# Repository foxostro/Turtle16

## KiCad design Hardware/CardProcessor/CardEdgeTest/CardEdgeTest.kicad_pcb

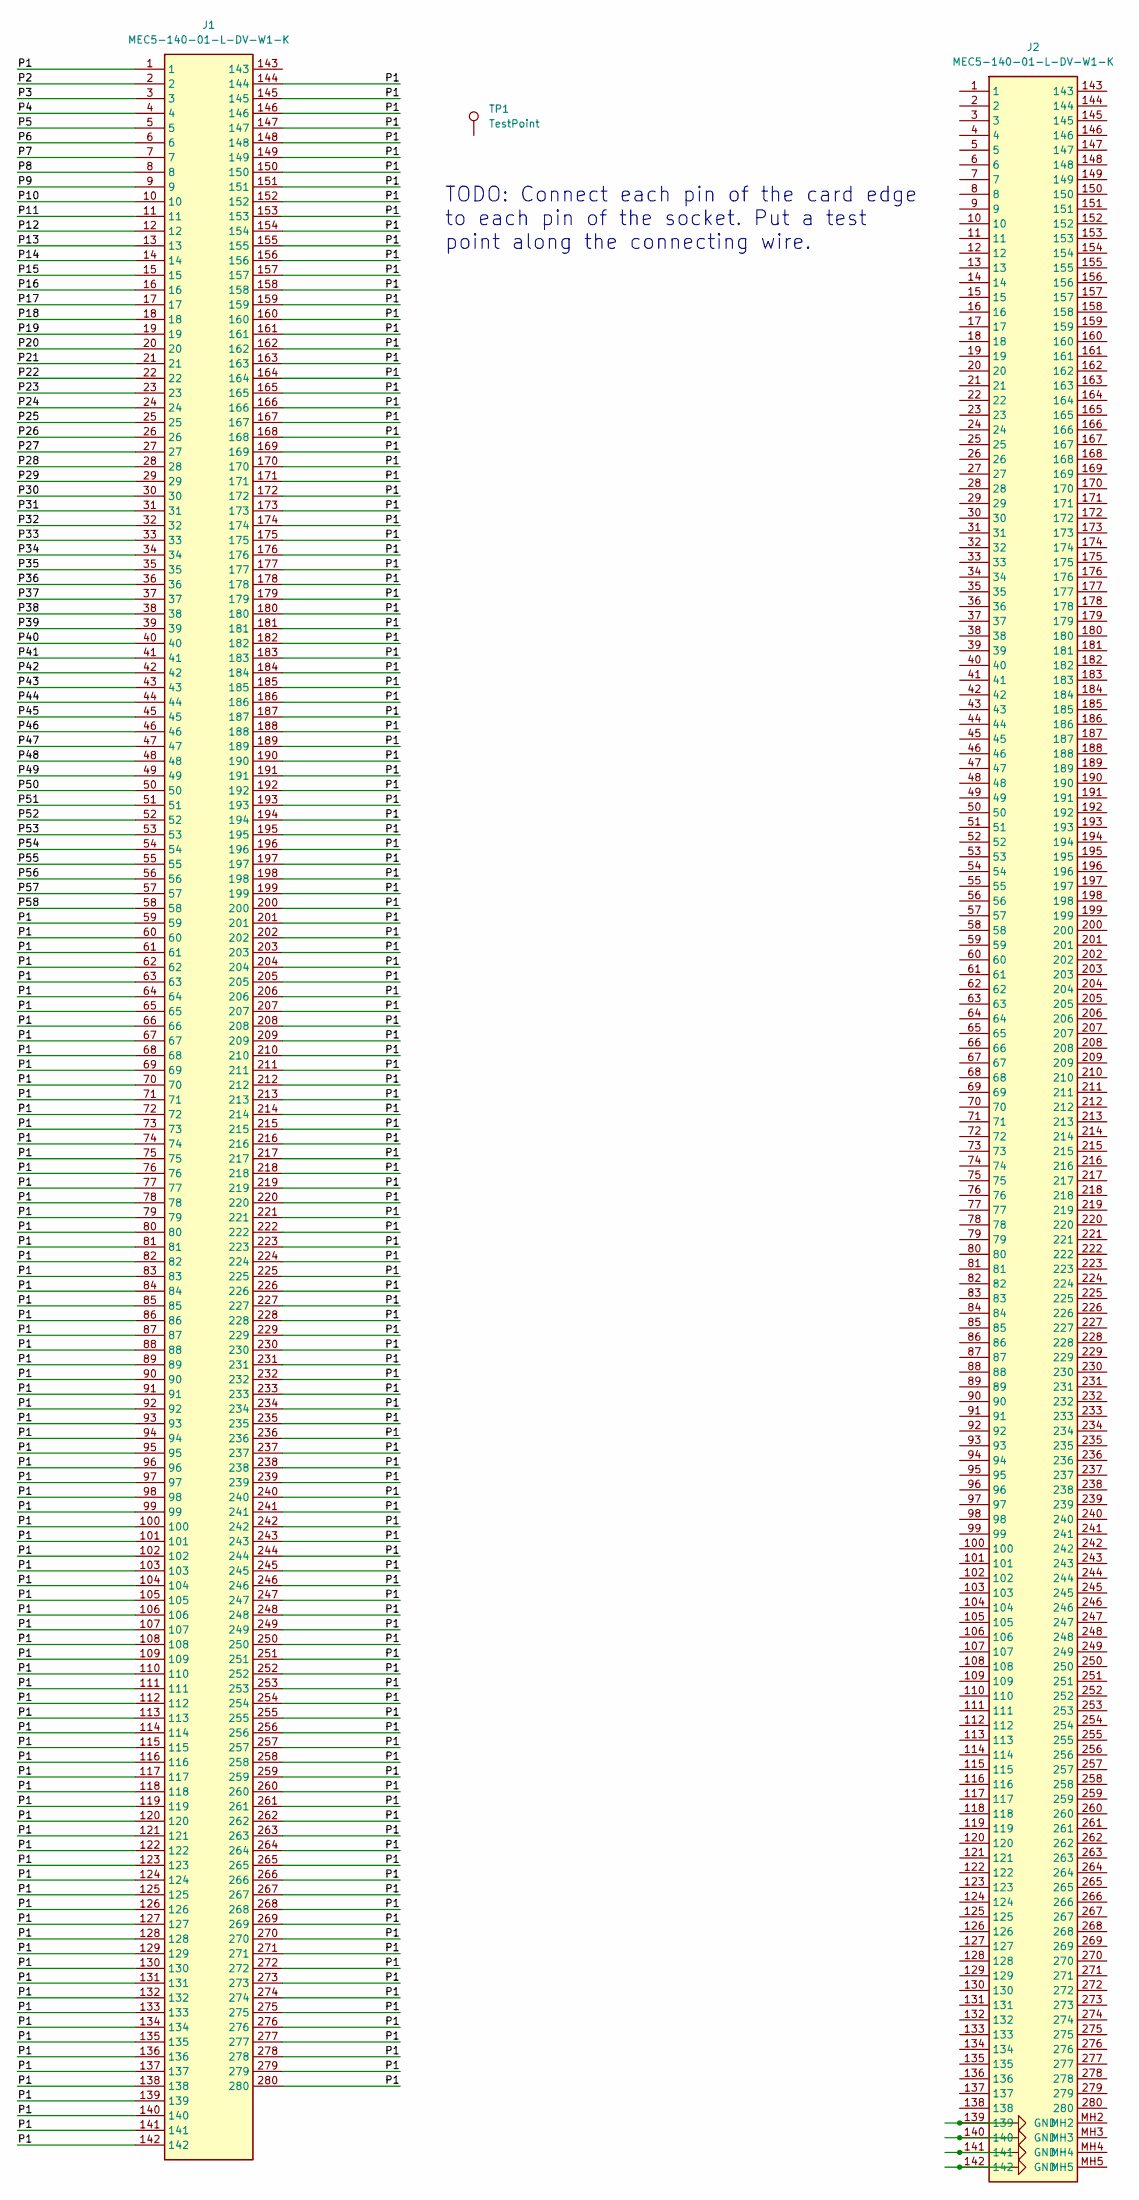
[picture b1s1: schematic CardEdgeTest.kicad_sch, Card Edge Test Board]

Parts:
J1: MEC5-140-01-L-DV-W1-K; MEC5-140-01-L-DV-W1-K_Edge; Mouser Part Number 200-MEC514001LDVW1K
J2: MEC5-140-01-L-DV-W1-K; MEC514001LDVW1K; Mouser Part Number 200-MEC514001LDVW1K
TP1: TestPoint; TestPoint_Pad_D1.0mm

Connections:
/P1: J1.1, J1.59, J1.60, J1.61, J1.62, J1.63, J1.64, J1.65, J1.66, J1.67, J1.68, J1.69, J1.70, J1.71, J1.72, J1.73, J1.74, J1.75, J1.76, J1.77, J1.78, J1.79, J1.80, J1.81, J1.82, J1.83, J1.84, J1.85, J1.86, J1.87, J1.88, J1.89, J1.90, J1.91, J1.92, J1.93, J1.94, J1.95, J1.96, J1.97, J1.98, J1.99, J1.100, J1.101, J1.102, J1.103, J1.104, J1.105, J1.106, J1.107, J1.108, J1.109, J1.110, J1.111, J1.112, J1.113, J1.114, J1.115, J1.116, J1.117, J1.118, J1.119, J1.120, J1.121, J1.122, J1.123, J1.124, J1.125, J1.126, J1.127, J1.128, J1.129, J1.130, J1.131, J1.132, J1.133, J1.134, J1.135, J1.136, J1.137, J1.138, J1.139, J1.140, J1.141, J1.142, J1.144, J1.145, J1.146, J1.147, J1.148, J1.149, J1.150, J1.151, J1.152, J1.153, J1.154, J1.155, J1.156, J1.157, J1.158, J1.159, J1.160, J1.161, J1.162, J1.163, J1.164, J1.165, J1.166, J1.167, J1.168, J1.169, J1.170, J1.171, J1.172, J1.173, J1.174, J1.175, J1.176, J1.177, J1.178, J1.179, J1.180, J1.181, J1.182, J1.183, J1.184, J1.185, J1.186, J1.187, J1.188, J1.189, J1.190, J1.191, J1.192, J1.193, J1.194, J1.195, J1.196, J1.197, J1.198, J1.199, J1.200, J1.201, J1.202, J1.203, J1.204, J1.205, J1.206, J1.207, J1.208, J1.209, J1.210, J1.211, J1.212, J1.213, J1.214, J1.215, J1.216, J1.217, J1.218, J1.219, J1.220, J1.221, J1.222, J1.223, J1.224, J1.225, J1.226, J1.227, J1.228, J1.229, J1.230, J1.231, J1.232, J1.233, J1.234, J1.235, J1.236, J1.237, J1.238, J1.239, J1.240, J1.241, J1.242, J1.243, J1.244, J1.245, J1.246, J1.247, J1.248, J1.249, J1.250, J1.251, J1.252, J1.253, J1.254, J1.255, J1.256, J1.257, J1.258, J1.259, J1.260, J1.261, J1.262, J1.263, J1.264, J1.265, J1.266, J1.267, J1.268, J1.269, J1.270, J1.271, J1.272, J1.273, J1.274, J1.275, J1.276, J1.277, J1.278, J1.279, J1.280
/P2: J1.2
/P3: J1.3
/P4: J1.4
/P5: J1.5
/P6: J1.6
/P7: J1.7
/P8: J1.8
/P9: J1.9
/P10: J1.10
/P11: J1.11
/P12: J1.12
/P13: J1.13
/P14: J1.14
/P15: J1.15
/P16: J1.16
/P17: J1.17
/P18: J1.18
/P19: J1.19
/P20: J1.20
/P21: J1.21
/P22: J1.22
/P23: J1.23
/P24: J1.24
/P25: J1.25
/P26: J1.26
/P27: J1.27
/P28: J1.28
/P29: J1.29
/P30: J1.30
/P31: J1.31
/P32: J1.32
/P33: J1.33
/P34: J1.34
/P35: J1.35
/P36: J1.36
/P37: J1.37
/P38: J1.38
/P39: J1.39
/P40: J1.40
/P41: J1.41
/P42: J1.42
/P43: J1.43
/P44: J1.44
/P45: J1.45
/P46: J1.46
/P47: J1.47
/P48: J1.48
/P49: J1.49
/P50: J1.50
/P51: J1.51
/P52: J1.52
/P53: J1.53
/P54: J1.54
/P55: J1.55
/P56: J1.56
/P57: J1.57
/P58: J1.58
GND: J2.139, J2.140, J2.141, J2.142

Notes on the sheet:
TODO: Connect each pin of the card edge to each pin of the socket. Put a test point along the connecting wire.

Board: 2 copper layers, 3 parts (0 on the bottom side), 2 nets, no tracks yet.

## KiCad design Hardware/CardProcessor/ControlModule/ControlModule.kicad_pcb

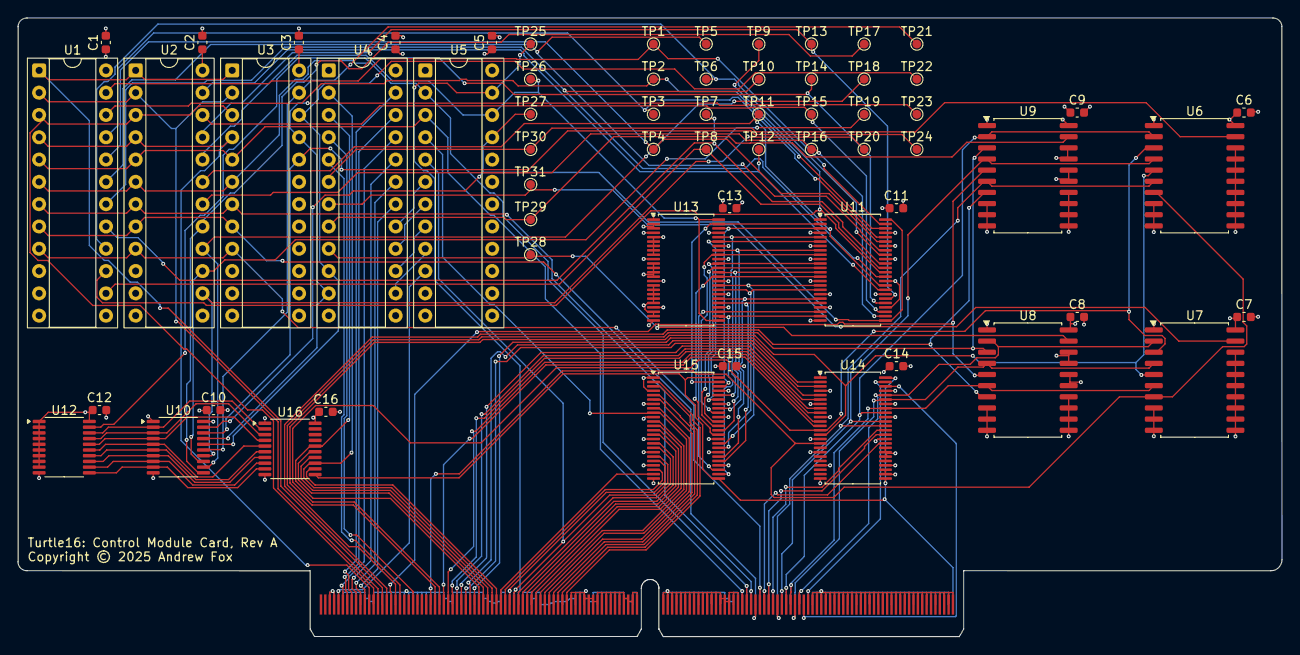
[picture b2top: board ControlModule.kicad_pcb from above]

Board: 4 copper layers, 144.0 x 70.5 mm, 64 parts (0 on the bottom side), 126 nets.

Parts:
C1, C2, C3, C4, C5, C6, C7, C8, C9, C10, C11, C12, C13, C14, C15, C16: 0.1uF; C_0603_1608Metric
J1: MEC5-140-01-L-DV-W1-K; MEC5-140-01-L-DV-W1-K_Edge
TP1: Ctl_Mid0; TestPoint_Pad_D1.0mm
TP2: Ctl_Mid1; TestPoint_Pad_D1.0mm
TP3: Ctl_Mid2; TestPoint_Pad_D1.0mm
TP4: Ctl_Mid3; TestPoint_Pad_D1.0mm
TP5: Ctl_Mid4; TestPoint_Pad_D1.0mm
TP6: Ctl_Mid5; TestPoint_Pad_D1.0mm
TP7: Ctl_Mid6; TestPoint_Pad_D1.0mm
TP8: Ctl_Mid7; TestPoint_Pad_D1.0mm
TP9: Ctl_Mid8; TestPoint_Pad_D1.0mm
TP10: Ctl_Mid9; TestPoint_Pad_D1.0mm
TP11: Ctl_Mid10; TestPoint_Pad_D1.0mm
TP12: Ctl_Mid11; TestPoint_Pad_D1.0mm
TP13: Ctl_Mid12; TestPoint_Pad_D1.0mm
TP14: Ctl_Mid13; TestPoint_Pad_D1.0mm
TP15: Ctl_Mid14; TestPoint_Pad_D1.0mm
TP16: Ctl_Mid15; TestPoint_Pad_D1.0mm
TP17: Ctl_Mid16; TestPoint_Pad_D1.0mm
TP18: Ctl_Mid17; TestPoint_Pad_D1.0mm
TP19: Ctl_Mid18; TestPoint_Pad_D1.0mm
TP20: Ctl_Mid19; TestPoint_Pad_D1.0mm
TP21: Ctl_Mid20; TestPoint_Pad_D1.0mm
TP22: Ctl_Mid21; TestPoint_Pad_D1.0mm
TP23: Ctl_Mid22; TestPoint_Pad_D1.0mm
TP24: Ctl_Mid23; TestPoint_Pad_D1.0mm
TP25: STALL; TestPoint_Pad_D1.0mm
TP26: ~{FLUSH}; TestPoint_Pad_D1.0mm
TP27: FLUSH; TestPoint_Pad_D1.0mm
TP28: SEL_B_MATCHES_SEL_C_MEM; TestPoint_Pad_D1.0mm
TP29: SEL_A_MATCHES_SEL_C_MEM; TestPoint_Pad_D1.0mm
TP30: SEL_A_MATCHES_SEL_C_EX; TestPoint_Pad_D1.0mm
TP31: SEL_B_MATCHES_SEL_C_EX; TestPoint_Pad_D1.0mm
U1, U2, U3, U4, U5: ATF22V10C-7PX; DIP-24_W7.62mm_Socket
U6, U7, U8, U9: 74F521; SOIC-20W_7.5x12.8mm_P1.27mm
U10, U12: 74ABT245; TSSOP-20_4.4x6.5mm_P0.65mm
U11, U13: 74ABT16245; TSSOP-48_6.1x12.5mm_P0.5mm
U14, U15: 74ABT16374; TSSOP-48_6.1x12.5mm_P0.5mm
U16: 74ABT574; TSSOP-20_4.4x6.5mm_P0.65mm

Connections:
/CardEdgeControl/Carry: J1.23, U1.4 (IN), U2.4 (IN), U3.4 (IN)
/CardEdgeControl/Ctl_MEM17: J1.43, U4.4 (IN)
/CardEdgeControl/Ctl_MEM20: J1.37, U4.5 (IN)
/CardEdgeControl/FWD_A: J1.11, U4.21 (I/O)
/CardEdgeControl/FWD_B: J1.17, U4.20 (I/O)
/CardEdgeControl/FWD_EX_TO_A: J1.13, U4.22 (I/O)
/CardEdgeControl/FWD_EX_TO_B: J1.19, U4.19 (I/O)
/CardEdgeControl/FWD_MEM_TO_A: J1.15, U4.23 (I/O)
/CardEdgeControl/FWD_MEM_TO_B: J1.21, U4.18 (I/O)
/CardEdgeControl/Ins_ID0: J1.213, J1.214, U14.47 (1D1)
/CardEdgeControl/Ins_ID1: J1.211, J1.212, U14.46 (1D2)
/CardEdgeControl/Ins_ID2: J1.209, J1.210, U7.2 (P0), U8.2 (P0), U14.44 (1D3)
/CardEdgeControl/Ins_ID3: J1.207, J1.208, U7.4 (P1), U8.4 (P1), U14.43 (1D4)
/CardEdgeControl/Ins_ID4: J1.205, J1.206, U7.6 (P2), U8.6 (P2), U14.41 (1D5)
/CardEdgeControl/Ins_ID5: J1.203, J1.204, U6.2 (P0), U9.2 (P0), U14.40 (1D6)
/CardEdgeControl/Ins_ID6: J1.201, J1.202, U6.4 (P1), U9.4 (P1), U14.38 (1D7)
/CardEdgeControl/Ins_ID7: J1.199, J1.200, U6.6 (P2), U9.6 (P2), U14.37 (1D8)
/CardEdgeControl/Ins_ID8: J1.197, J1.198, U14.36 (2D1)
/CardEdgeControl/Ins_ID9: J1.195, J1.196, U14.35 (2D2)
/CardEdgeControl/Ins_ID10: J1.193, J1.194, U14.33 (2D3)
/CardEdgeControl/Ins_ID11: J1.191, J1.192, U1.9 (IN), U2.9 (IN), U3.9 (IN)
/CardEdgeControl/Ins_ID12: J1.189, J1.190, U1.8 (IN), U2.8 (IN), U3.8 (IN)
/CardEdgeControl/Ins_ID13: J1.187, J1.188, U1.7 (IN), U2.7 (IN), U3.7 (IN)
/CardEdgeControl/Ins_ID14: J1.185, J1.186, U1.6 (IN), U2.6 (IN), U3.6 (IN), U5.2 (IN)
/CardEdgeControl/Ins_ID15: J1.183, J1.184, U1.5 (IN), U2.5 (IN), U3.5 (IN), U5.3 (IN)
/CardEdgeControl/N: J1.29, U1.1 (IN/CLK), U2.1 (IN/CLK), U3.1 (IN/CLK)
/CardEdgeControl/OVF: J1.27, U1.2 (IN), U2.2 (IN), U3.2 (IN)
/CardEdgeControl/Phi1c: J1.280, U14.25 (2CLK), U14.48 (1CLK), U15.25 (2CLK), U15.48 (1CLK), U16.11 (Cp)
/CardEdgeControl/SelC_MEM0: J1.35, U8.3 (Q0), U9.3 (Q0)
/CardEdgeControl/SelC_MEM1: J1.33, U8.5 (Q1), U9.5 (Q1)
/CardEdgeControl/SelC_MEM2: J1.31, U8.7 (Q2), U9.7 (Q2)
/CardEdgeControl/Z: J1.25, U1.3 (IN), U2.3 (IN), U3.3 (IN)
/CardEdgeControl/~RST_sync: J1.9, J1.10, U5.10 (IN)
/ID/Ctl_EX0: J1.113, U15.2 (1Q1)
/ID/Ctl_EX1: J1.111, U15.3 (1Q2)
/ID/Ctl_EX2: J1.109, U15.5 (1Q3)
/ID/Ctl_EX3: J1.107, U15.6 (1Q4)
/ID/Ctl_EX4: J1.105, U15.8 (1Q5)
/ID/Ctl_EX5: J1.103, U5.4 (IN), U15.9 (1Q6)
/ID/Ctl_EX6: J1.101, U15.11 (1Q7)
/ID/Ctl_EX7: J1.99, U15.12 (1Q8)
/ID/Ctl_EX8: J1.97, U15.13 (2Q1)
/ID/Ctl_EX9: J1.95, U15.14 (2Q2)
/ID/Ctl_EX10: J1.93, U15.16 (2Q3)
/ID/Ctl_EX11: J1.91, U15.17 (2Q4)
/ID/Ctl_EX12: J1.89, J1.90, U5.5 (IN), U15.19 (2Q5)
/ID/Ctl_EX13: J1.87, J1.88, U15.20 (2Q6)
/ID/Ctl_EX14: J1.85, U15.22 (2Q7)
/ID/Ctl_EX15: J1.83, U15.23 (2Q8)
/ID/Ctl_EX16: J1.81, U16.12 (Q7)
/ID/Ctl_EX17: J1.79, U4.2 (IN), U16.13 (Q6)
/ID/Ctl_EX18: J1.77, U16.14 (Q5)
/ID/Ctl_EX19: J1.75, U16.15 (Q4)
/ID/Ctl_EX20: J1.73, U4.3 (IN), U16.16 (Q3)
/ID/Ctl_Mid0: TP1.1, U1.23 (I/O), U11.47 (1A1)
/ID/Ctl_Mid1: TP2.1, U1.22 (I/O), U11.46 (1A2)
/ID/Ctl_Mid2: TP3.1, U1.21 (I/O), U11.44 (1A3)
/ID/Ctl_Mid3: TP4.1, U1.20 (I/O), U11.43 (1A4)
/ID/Ctl_Mid4: TP5.1, U1.19 (I/O), U11.41 (1A5)
/ID/Ctl_Mid5: TP6.1, U1.16 (I/O), U11.40 (1A6)
/ID/Ctl_Mid6: TP7.1, U1.17 (I/O), U11.38 (1A7)
/ID/Ctl_Mid7: TP8.1, U1.14 (I/O), U11.37 (1A8)
/ID/Ctl_Mid8: TP9.1, U1.15 (I/O), U11.36 (2A1)
/ID/Ctl_Mid9: TP10.1, U1.18 (I/O), U11.35 (2A2)
/ID/Ctl_Mid10: TP11.1, U2.19 (I/O), U11.33 (2A3)
/ID/Ctl_Mid11: TP12.1, U2.23 (I/O), U11.32 (2A4)
/ID/Ctl_Mid12: TP13.1, U2.21 (I/O), U11.30 (2A5)
/ID/Ctl_Mid13: TP14.1, U2.20 (I/O), U11.29 (2A6)
/ID/Ctl_Mid14: TP15.1, U2.22 (I/O), U11.27 (2A7)
/ID/Ctl_Mid15: TP16.1, U2.18 (I/O), U11.26 (2A8)
/ID/Ctl_Mid16: TP17.1, U2.17 (I/O), U10.11 (B7)
/ID/Ctl_Mid17: TP18.1, U2.16 (I/O), U10.12 (B6)
/ID/Ctl_Mid18: TP19.1, U2.15 (I/O), U10.13 (B5)
/ID/Ctl_Mid19: TP20.1, U2.14 (I/O), U10.14 (B4)
/ID/Ctl_Mid20: TP21.1, U3.23 (I/O), U10.15 (B3)
/ID/Ctl_Mid21: TP22.1, U3.22 (I/O), U4.10 (IN), U10.16 (B2)
/ID/Ctl_Mid22: TP23.1, U3.21 (I/O), U4.11 (IN), U10.17 (B1)
/ID/Ctl_Mid23: TP24.1, U3.20 (I/O), U10.18 (B0)
/ID/Hazard Control/FLUSH: TP27.1, U5.21 (I/O), U10.19 (CE), U11.25 (2~OE), U11.48 (1~OE)
/ID/Hazard Control/Hazard Control Comparators/SEL_A_MATCHES_SEL_C_EX: TP30.1, U4.6 (IN), U6.19 (~P=Q)
/ID/Hazard Control/Hazard Control Comparators/SEL_A_MATCHES_SEL_C_MEM: TP29.1, U4.8 (IN), U9.19 (~P=Q)
/ID/Hazard Control/Hazard Control Comparators/SEL_B_MATCHES_SEL_C_EX: TP31.1, U4.7 (IN), U7.19 (~P=Q)
/ID/Hazard Control/Hazard Control Comparators/SEL_B_MATCHES_SEL_C_MEM: TP28.1, U4.9 (IN), U8.19 (~P=Q)
/ID/Hazard Control/STALL: J1.92, TP25.1, U5.23 (I/O)
/ID/Hazard Control/~FLUSH: TP26.1, U5.22 (I/O), U12.19 (CE), U13.25 (2~OE), U13.48 (1~OE)
/ID/ID Flush/Ctl_ID0: U11.2 (1B1), U13.47 (1A1), U15.47 (1D1)
/ID/ID Flush/Ctl_ID1: U11.3 (1B2), U13.46 (1A2), U15.46 (1D2)
/ID/ID Flush/Ctl_ID2: U11.5 (1B3), U13.44 (1A3), U15.44 (1D3)
/ID/ID Flush/Ctl_ID3: U11.6 (1B4), U13.43 (1A4), U15.43 (1D4)
/ID/ID Flush/Ctl_ID4: U11.8 (1B5), U13.41 (1A5), U15.41 (1D5)
/ID/ID Flush/Ctl_ID5: U11.9 (1B6), U13.40 (1A6), U15.40 (1D6)
/ID/ID Flush/Ctl_ID6: U11.11 (1B7), U13.38 (1A7), U15.38 (1D7)
/ID/ID Flush/Ctl_ID7: U11.12 (1B8), U13.37 (1A8), U15.37 (1D8)
/ID/ID Flush/Ctl_ID8: U11.13 (2B1), U13.36 (2A1), U15.36 (2D1)
/ID/ID Flush/Ctl_ID9: U11.14 (2B2), U13.35 (2A2), U15.35 (2D2)
/ID/ID Flush/Ctl_ID10: U11.16 (2B3), U13.33 (2A3), U15.33 (2D3)
/ID/ID Flush/Ctl_ID11: U11.17 (2B4), U13.32 (2A4), U15.32 (2D4)
/ID/ID Flush/Ctl_ID12: U11.19 (2B5), U13.30 (2A5), U15.30 (2D5)
/ID/ID Flush/Ctl_ID13: U11.20 (2B6), U13.29 (2A6), U15.29 (2D6)
/ID/ID Flush/Ctl_ID14: U11.22 (2B7), U13.27 (2A7), U15.27 (2D7)
/ID/ID Flush/Ctl_ID15: U11.23 (2B8), U13.26 (2A8), U15.26 (2D8)
/ID/ID Flush/Ctl_ID16: U10.9 (A7), U12.11 (B7), U16.9 (D7)
/ID/ID Flush/Ctl_ID17: U10.8 (A6), U12.12 (B6), U16.8 (D6)
/ID/ID Flush/Ctl_ID18: U10.7 (A5), U12.13 (B5), U16.7 (D5)
/ID/ID Flush/Ctl_ID19: U10.6 (A4), U12.14 (B4), U16.6 (D4)
/ID/ID Flush/Ctl_ID20: U10.5 (A3), U12.15 (B3), U16.5 (D3)
/ID/ID Flush/Ctl_ID21: U10.4 (A2), U12.16 (B2), U16.4 (D2)
/ID/ID Flush/Ctl_ID22: U10.3 (A1), U12.17 (B1), U16.3 (D1)
/ID/ID Flush/Ctl_ID23: U10.2 (A0), U12.18 (B0), U16.2 (D0)
/ID/Ins_EX0: J1.71, U14.2 (1Q1)
/ID/Ins_EX1: J1.69, U14.3 (1Q2)
/ID/Ins_EX2: J1.67, U14.5 (1Q3)
/ID/Ins_EX3: J1.65, U14.6 (1Q4)
/ID/Ins_EX4: J1.63, U14.8 (1Q5)
/ID/Ins_EX5: J1.61, U14.9 (1Q6)
/ID/Ins_EX6: J1.59, U14.11 (1Q7)
/ID/Ins_EX7: J1.57, U14.12 (1Q8)
/ID/Ins_EX8: J1.55, U6.3 (Q0), U7.3 (Q0), U14.13 (2Q1)
/ID/Ins_EX9: J1.53, U6.5 (Q1), U7.5 (Q1), U14.14 (2Q2)
/ID/Ins_EX10: J1.51, U6.7 (Q2), U7.7 (Q2), U14.16 (2Q3)
GND: C1.2, C2.2, C3.2, C4.2, C5.2, C6.2, C7.2, C8.2, C9.2, C10.2, C11.2, C12.2, C13.2, C14.2, C15.2, C16.2, J1.12, J1.14, J1.16, J1.18, J1.20, J1.22, J1.24, J1.26, J1.28, J1.30, J1.32, J1.34, J1.36, J1.38, J1.40, J1.42, J1.44, J1.46, J1.48, J1.50, J1.52, J1.54, J1.56, J1.58, J1.60, J1.62, J1.64, J1.66, J1.68, J1.70, J1.72, J1.74, J1.76, J1.78, J1.80, J1.82, J1.84, J1.86, J1.94, J1.96, J1.98, J1.100, J1.102, J1.104, J1.106, J1.108, J1.110, J1.112, J1.114, J1.115, J1.116, J1.117, J1.118, J1.119, J1.120, J1.121, J1.122, J1.123, J1.124, J1.125, J1.126, J1.127, J1.128, J1.129, J1.130, J1.131, J1.132, J1.133, J1.134, J1.135, J1.136, J1.137, J1.138, J1.139, J1.140, J1.141, J1.142, J1.143, J1.144, J1.145, J1.146, J1.147, J1.148, J1.149, J1.150, J1.151, J1.152, J1.153, J1.154, J1.155, J1.156, J1.157, J1.158, J1.159, J1.160, J1.161, J1.162, J1.163, J1.164, J1.165, J1.166, J1.167, J1.168, J1.169, J1.170, J1.171, J1.172, J1.173, J1.174, J1.175, J1.176, J1.177, J1.178, J1.179, J1.180, J1.181, J1.182, J1.215, J1.216, J1.217, J1.218, J1.219, J1.220, J1.221, J1.222, J1.223, J1.224, J1.225, J1.226, J1.227, J1.228, J1.229, J1.230, J1.231, J1.232, J1.233, J1.234, J1.235, J1.236, J1.237, J1.238, J1.239, J1.240, J1.241, J1.242, J1.243, J1.244, J1.245, J1.246, J1.247, J1.248, J1.249, J1.250, J1.251, J1.252, J1.253, J1.254, J1.255, J1.256, J1.257, J1.258, J1.259, J1.260, J1.261, J1.262, J1.263, J1.264, J1.265, J1.266, J1.267, J1.268, J1.269, J1.270, J1.271, J1.272, J1.273, J1.274, J1.275, J1.276, J1.277, J1.278, J1.279, U1.10 (IN), U1.11 (IN), U1.12 (GND), U2.10 (IN), U2.11 (IN), U2.12 (GND), U3.10 (IN), U3.11 (IN), U3.12 (GND), U4.1 (IN/CLK), U4.12 (GND), U5.1 (IN/CLK), U5.12 (GND), U5.15 (I/O), U6.1 (~OE), U6.8 (P3), U6.9 (Q3), U6.10 (GND), U6.11 (P4), U6.12 (Q4), U6.13 (P5), U6.14 (Q5), U6.15 (P6), U6.16 (Q6), U6.17 (P7), U6.18 (Q7), U7.1 (~OE), U7.8 (P3), U7.9 (Q3), U7.10 (GND), U7.11 (P4), U7.12 (Q4), U7.13 (P5), U7.14 (Q5), U7.15 (P6), U7.16 (Q6), U7.17 (P7), U7.18 (Q7), U8.1 (~OE), U8.8 (P3), U8.9 (Q3), U8.10 (GND), U8.11 (P4), U8.12 (Q4), U8.13 (P5), U8.14 (Q5), U8.15 (P6), U8.16 (Q6), U8.17 (P7), U8.18 (Q7), U9.1 (~OE), U9.8 (P3), U9.9 (Q3), U9.10 (GND), U9.11 (P4), U9.12 (Q4), U9.13 (P5), U9.14 (Q5), U9.15 (P6), U9.16 (Q6), U9.17 (P7), U9.18 (Q7), U10.1 (A->B), U10.10 (GND), U11.4 (GND), U11.10 (GND), U11.15 (GND), U11.21 (GND), U11.28 (GND), U11.34 (GND), U11.39 (GND), U11.45 (GND), U12.10 (GND), U13.1 (1DIR), U13.4 (GND), U13.10 (GND), U13.15 (GND), U13.21 (GND), U13.24 (2DIR), U13.28 (GND), U13.34 (GND), U13.39 (GND), U13.45 (GND), U14.1 (1~OE), U14.4 (GND), U14.10 (GND), U14.15 (GND), U14.21 (GND), U14.24 (2~OE), U14.28 (GND), U14.34 (GND), U14.39 (GND), U14.45 (GND), U15.1 (1~OE), U15.4 (GND), U15.10 (GND), U15.15 (GND), U15.21 (GND), U15.24 (2~OE), U15.28 (GND), U15.34 (GND), U15.39 (GND), U15.45 (GND), U16.1 (OE), U16.10 (GND)
unnamed: U4.14 (I/O), U5.9 (IN)
unnamed: U4.15 (I/O), U5.8 (IN)
unnamed: U4.16 (I/O), U5.7 (IN)
unnamed: U4.17 (I/O), U5.6 (IN)
VCC: C1.1, C2.1, C3.1, C4.1, C5.1, C6.1, C7.1, C8.1, C9.1, C10.1, C11.1, C12.1, C13.1, C14.1, C15.1, C16.1, J1.5, J1.6, J1.7, J1.8, U1.24 (VCC), U2.24 (VCC), U3.24 (VCC), U4.24 (VCC), U5.24 (VCC), U6.20 (VCC), U7.20 (VCC), U8.20 (VCC), U9.20 (VCC), U10.20 (VCC), U11.1 (1DIR), U11.7 (VCC), U11.18 (VCC), U11.24 (2DIR), U11.31 (VCC), U11.42 (VCC), U12.1 (A->B), U12.2 (A0), U12.3 (A1), U12.4 (A2), U12.5 (A3), U12.6 (A4), U12.7 (A5), U12.8 (A6), U12.9 (A7), U12.20 (VCC), U13.2 (1B1), U13.3 (1B2), U13.5 (1B3), U13.6 (1B4), U13.7 (VCC), U13.8 (1B5), U13.9 (1B6), U13.11 (1B7), U13.12 (1B8), U13.13 (2B1), U13.14 (2B2), U13.16 (2B3), U13.17 (2B4), U13.18 (VCC), U13.19 (2B5), U13.20 (2B6), U13.22 (2B7), U13.23 (2B8), U13.31 (VCC), U13.42 (VCC), U14.7 (VCC), U14.18 (VCC), U14.26 (2D8), U14.27 (2D7), U14.29 (2D6), U14.30 (2D5), U14.31 (VCC), U14.32 (2D4), U14.42 (VCC), U15.7 (VCC), U15.18 (VCC), U15.31 (VCC), U15.42 (VCC), U16.20 (VCC)

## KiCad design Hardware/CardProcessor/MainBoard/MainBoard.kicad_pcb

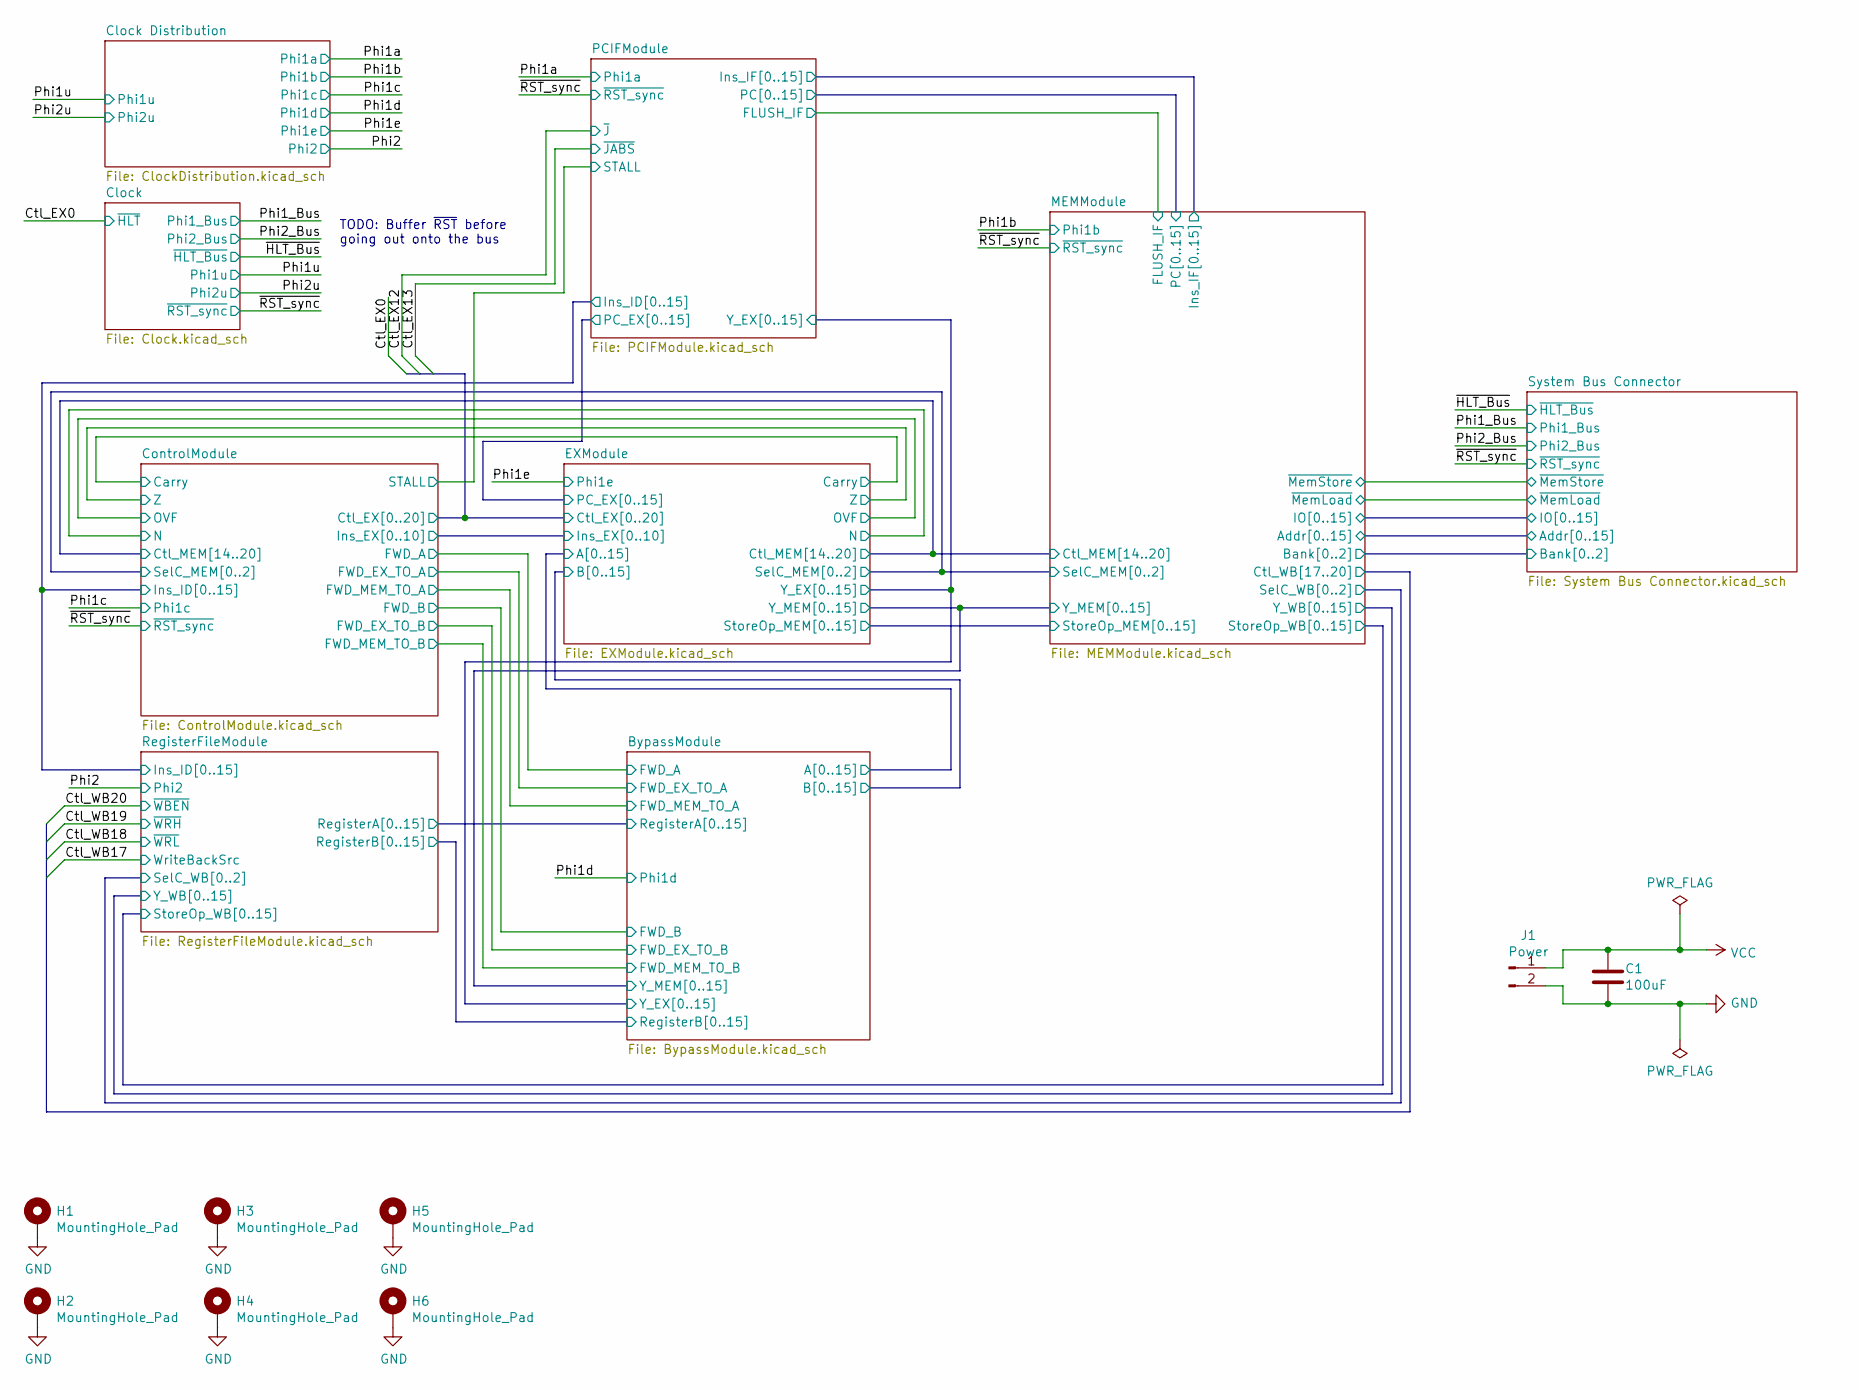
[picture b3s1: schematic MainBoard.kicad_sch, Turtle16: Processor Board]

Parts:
C1: 100uF; C_1206_3216Metric; Manufacturer# AMK316ABJ107ML-T; Mouser# 963-AMK316ABJ107ML-T
H1, H2, H3, H4, H5, H6: MountingHole_Pad; MountingHole_3.2mm_M3_Pad
J1: Power; 172448-0002; Manufacturer# 172448-0002; Mouser# 538-172448-0002

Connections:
GND: C1.2, H1.1, H2.1, H3.1, H4.1, H5.1, H6.1, J1.2; also elsewhere on the board
VCC: C1.1, J1.1; also elsewhere on the board

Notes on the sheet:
TODO: Buffer ~{RST} before going out onto the bus

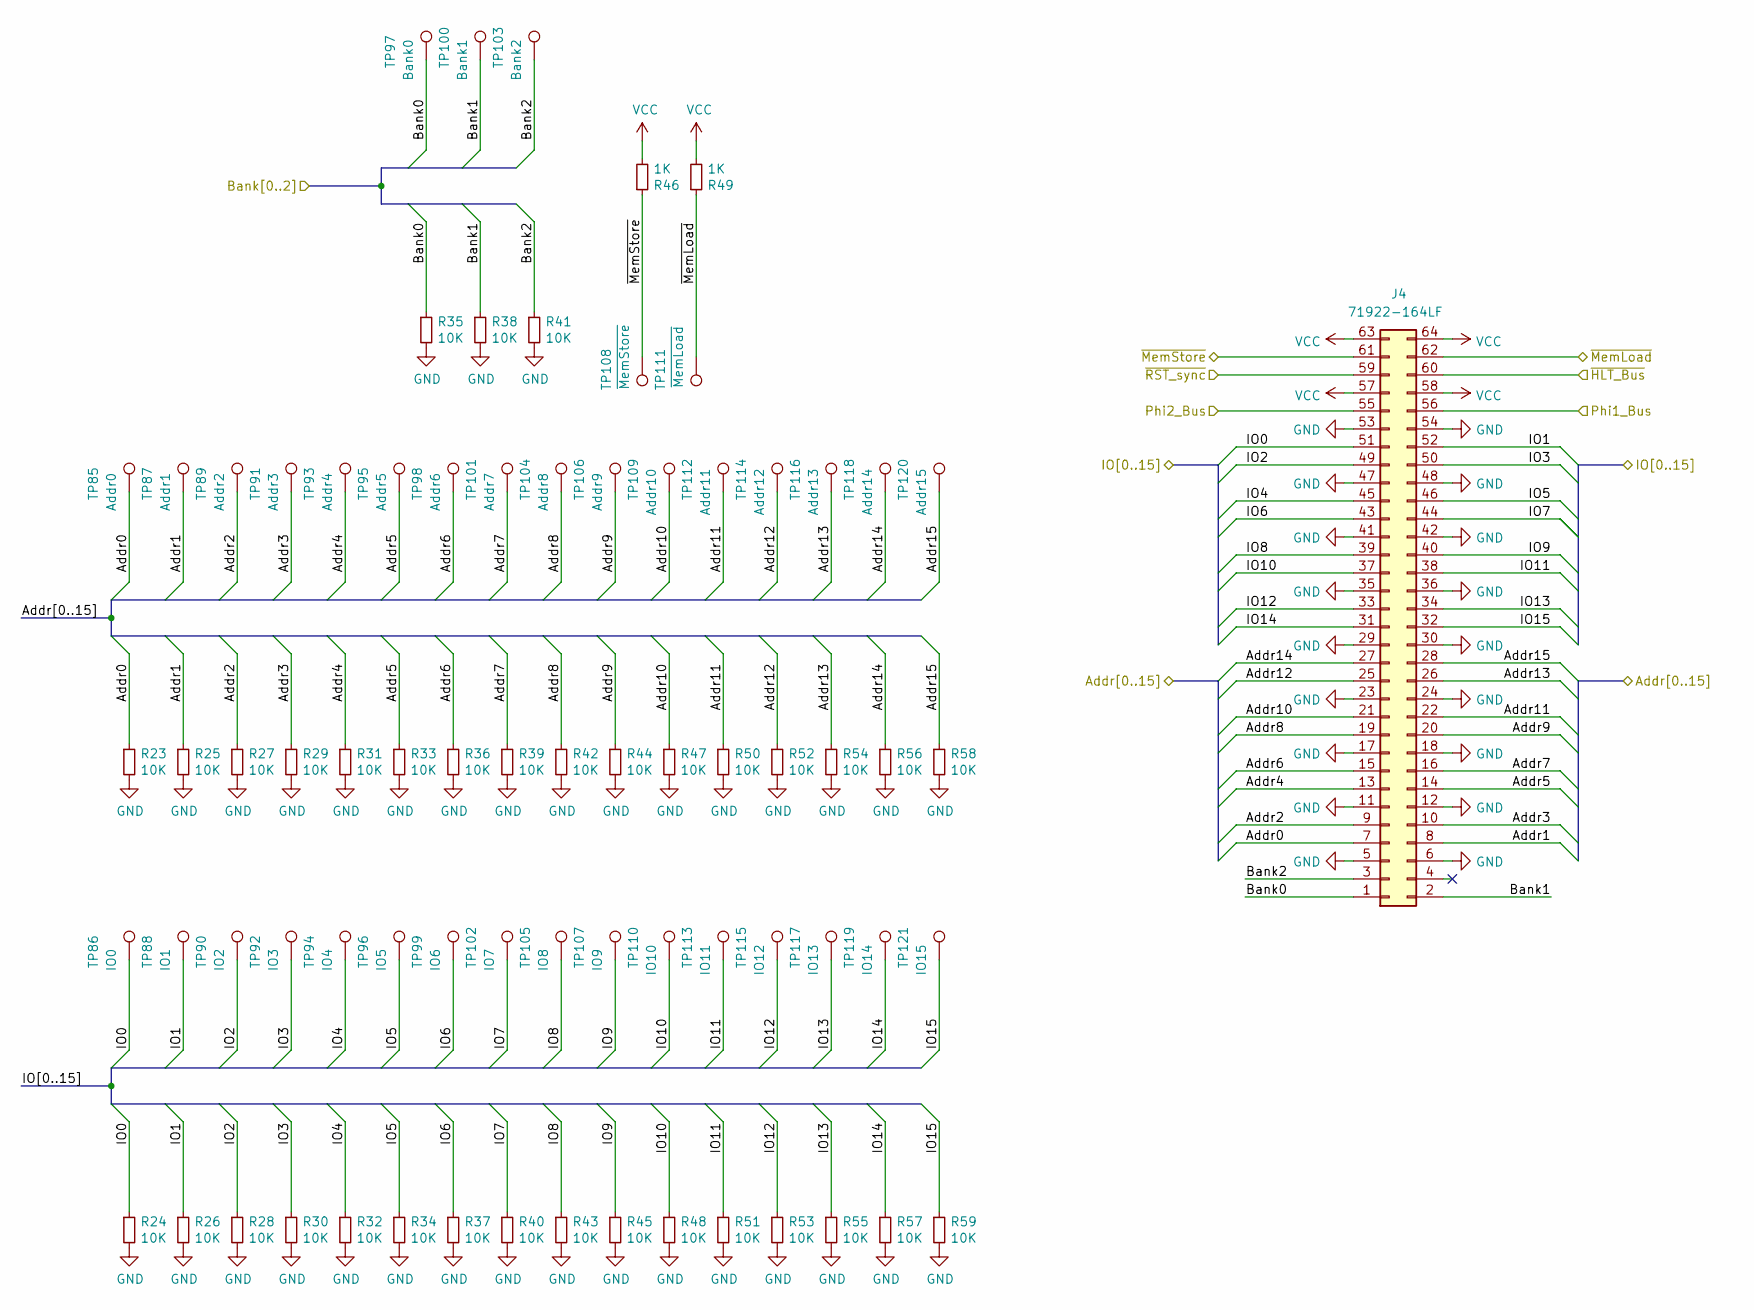
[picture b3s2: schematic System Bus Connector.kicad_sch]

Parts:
J4: 71922-164LF; IDC-Header_2x32_P2.54mm_Horizontal; Manufacturer# 71922-164LF; Mouser# 649-71922-164LF
R23, R24, R25, R26, R27, R28, R29, R30, R31, R32, R33, R34, R35, R36, R37, R38, R39, R40, R41, R42, R43, R44, R45, R47, R48, R50, R51, R52, R53, R54, R55, R56, R57, R58, R59: 10K; R_0603_1608Metric; Manufacturer# CR0603-FX-1002ELF; Mouser# 652-CR0603FX-1002ELF
R46, R49: 1K; R_0603_1608Metric; Manufacturer# CR0603-FX-1002ELF; Mouser# 652-CR0603FX-1002ELF
TP85: Addr0; TestPoint_Pad_D1.0mm
TP86: IO0; TestPoint_Pad_D1.0mm
TP87: Addr1; TestPoint_Pad_D1.0mm
TP88: IO1; TestPoint_Pad_D1.0mm
TP89: Addr2; TestPoint_Pad_D1.0mm
TP90: IO2; TestPoint_Pad_D1.0mm
TP91: Addr3; TestPoint_Pad_D1.0mm
TP92: IO3; TestPoint_Pad_D1.0mm
TP93: Addr4; TestPoint_Pad_D1.0mm
TP94: IO4; TestPoint_Pad_D1.0mm
TP95: Addr5; TestPoint_Pad_D1.0mm
TP96: IO5; TestPoint_Pad_D1.0mm
TP97: Bank0; TestPoint_Pad_D1.0mm
TP98: Addr6; TestPoint_Pad_D1.0mm
TP99: IO6; TestPoint_Pad_D1.0mm
TP100: Bank1; TestPoint_Pad_D1.0mm
TP101: Addr7; TestPoint_Pad_D1.0mm
TP102: IO7; TestPoint_Pad_D1.0mm
TP103: Bank2; TestPoint_Pad_D1.0mm
TP104: Addr8; TestPoint_Pad_D1.0mm
TP105: IO8; TestPoint_Pad_D1.0mm
TP106: Addr9; TestPoint_Pad_D1.0mm
TP107: IO9; TestPoint_Pad_D1.0mm
TP108: ~{MemStore}; TestPoint_Pad_D1.0mm
TP109: Addr10; TestPoint_Pad_D1.0mm
TP110: IO10; TestPoint_Pad_D1.0mm
TP111: ~{MemLoad}; TestPoint_Pad_D1.0mm
TP112: Addr11; TestPoint_Pad_D1.0mm
TP113: IO11; TestPoint_Pad_D1.0mm
TP114: Addr12; TestPoint_Pad_D1.0mm
TP115: IO12; TestPoint_Pad_D1.0mm
TP116: Addr13; TestPoint_Pad_D1.0mm
TP117: IO13; TestPoint_Pad_D1.0mm
TP118: Addr14; TestPoint_Pad_D1.0mm
TP119: IO14; TestPoint_Pad_D1.0mm
TP120: Addr15; TestPoint_Pad_D1.0mm
TP121: IO15; TestPoint_Pad_D1.0mm

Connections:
/Addr0: J4.7, R23.1, TP85.1; also elsewhere on the board
/Addr1: J4.8, R25.1, TP87.1; also elsewhere on the board
/Addr2: J4.9, R27.1, TP89.1; also elsewhere on the board
/Addr3: J4.10, R29.1, TP91.1; also elsewhere on the board
/Addr4: J4.13, R31.1, TP93.1; also elsewhere on the board
/Addr5: J4.14, R33.1, TP95.1; also elsewhere on the board
/Addr6: J4.15, R36.1, TP98.1; also elsewhere on the board
/Addr7: J4.16, R39.1, TP101.1; also elsewhere on the board
/Addr8: J4.19, R42.1, TP104.1; also elsewhere on the board
/Addr9: J4.20, R44.1, TP106.1; also elsewhere on the board
/Addr10: J4.21, R47.1, TP109.1; also elsewhere on the board
/Addr11: J4.22, R50.1, TP112.1; also elsewhere on the board
/Addr12: J4.25, R52.1, TP114.1; also elsewhere on the board
/Addr13: J4.26, R54.1, TP116.1; also elsewhere on the board
/Addr14: J4.27, R56.1, TP118.1; also elsewhere on the board
/Addr15: J4.28, R58.1, TP120.1; also elsewhere on the board
/Bank0: J4.1, R35.1, TP97.1; also elsewhere on the board
/Bank1: J4.2, R38.1, TP100.1; also elsewhere on the board
/Bank2: J4.3, R41.1, TP103.1; also elsewhere on the board
/IO0: J4.51, R24.1, TP86.1; also elsewhere on the board
/IO1: J4.52, R26.1, TP88.1; also elsewhere on the board
/IO2: J4.49, R28.1, TP90.1; also elsewhere on the board
/IO3: J4.50, R30.1, TP92.1; also elsewhere on the board
/IO4: J4.45, R32.1, TP94.1; also elsewhere on the board
/IO5: J4.46, R34.1, TP96.1; also elsewhere on the board
/IO6: J4.43, R37.1, TP99.1; also elsewhere on the board
/IO7: J4.44, R40.1, TP102.1; also elsewhere on the board
/IO8: J4.39, R43.1, TP105.1; also elsewhere on the board
/IO9: J4.40, R45.1, TP107.1; also elsewhere on the board
/IO10: J4.37, R48.1, TP110.1; also elsewhere on the board
/IO11: J4.38, R51.1, TP113.1; also elsewhere on the board
/IO12: J4.33, R53.1, TP115.1; also elsewhere on the board
/IO13: J4.34, R55.1, TP117.1; also elsewhere on the board
/IO14: J4.31, R57.1, TP119.1; also elsewhere on the board
/IO15: J4.32, R59.1, TP121.1; also elsewhere on the board
/Phi1_Bus: J4.56; also elsewhere on the board
/Phi2_Bus: J4.55; also elsewhere on the board
/~HLT_Bus: J4.60; also elsewhere on the board
/~MemLoad: J4.62, R49.1, TP111.1; also elsewhere on the board
/~MemStore: J4.61, R46.1, TP108.1; also elsewhere on the board
/~RST_sync: J4.59; also elsewhere on the board
GND: J4.5, J4.6, J4.11, J4.12, J4.17, J4.18, J4.23, J4.24, J4.29, J4.30, J4.35, J4.36, J4.41, J4.42, J4.47, J4.48, J4.53, J4.54, R23.2, R24.2, R25.2, R26.2, R27.2, R28.2, R29.2, R30.2, R31.2, R32.2, R33.2, R34.2, R35.2, R36.2, R37.2, R38.2, R39.2, R40.2, R41.2, R42.2, R43.2, R44.2, R45.2, R47.2, R48.2, R50.2, R51.2, R52.2, R53.2, R54.2, R55.2, R56.2, R57.2, R58.2, R59.2; also elsewhere on the board
VCC: J4.57, J4.58, J4.63, J4.64, R46.2, R49.2; also elsewhere on the board

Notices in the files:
Hardware/CardProcessor/CardEdgeTest/CardEdgeTest.kicad_pcb:
Copyright © 2025 Andrew Fox
Hardware/MonolithicProcessor/MainBoard/MainBoard.kicad_pcb:
Copyright © 2023 Andrew Fox
Hardware/PrototypeProcessor/BypassModule/BypassModule.kicad_pcb:
Copyright © 2022 Andrew Fox
Hardware/PrototypeProcessor/ClockModule/ClockModule.kicad_pcb:
Copyright © 2022-2023 Andrew Fox
